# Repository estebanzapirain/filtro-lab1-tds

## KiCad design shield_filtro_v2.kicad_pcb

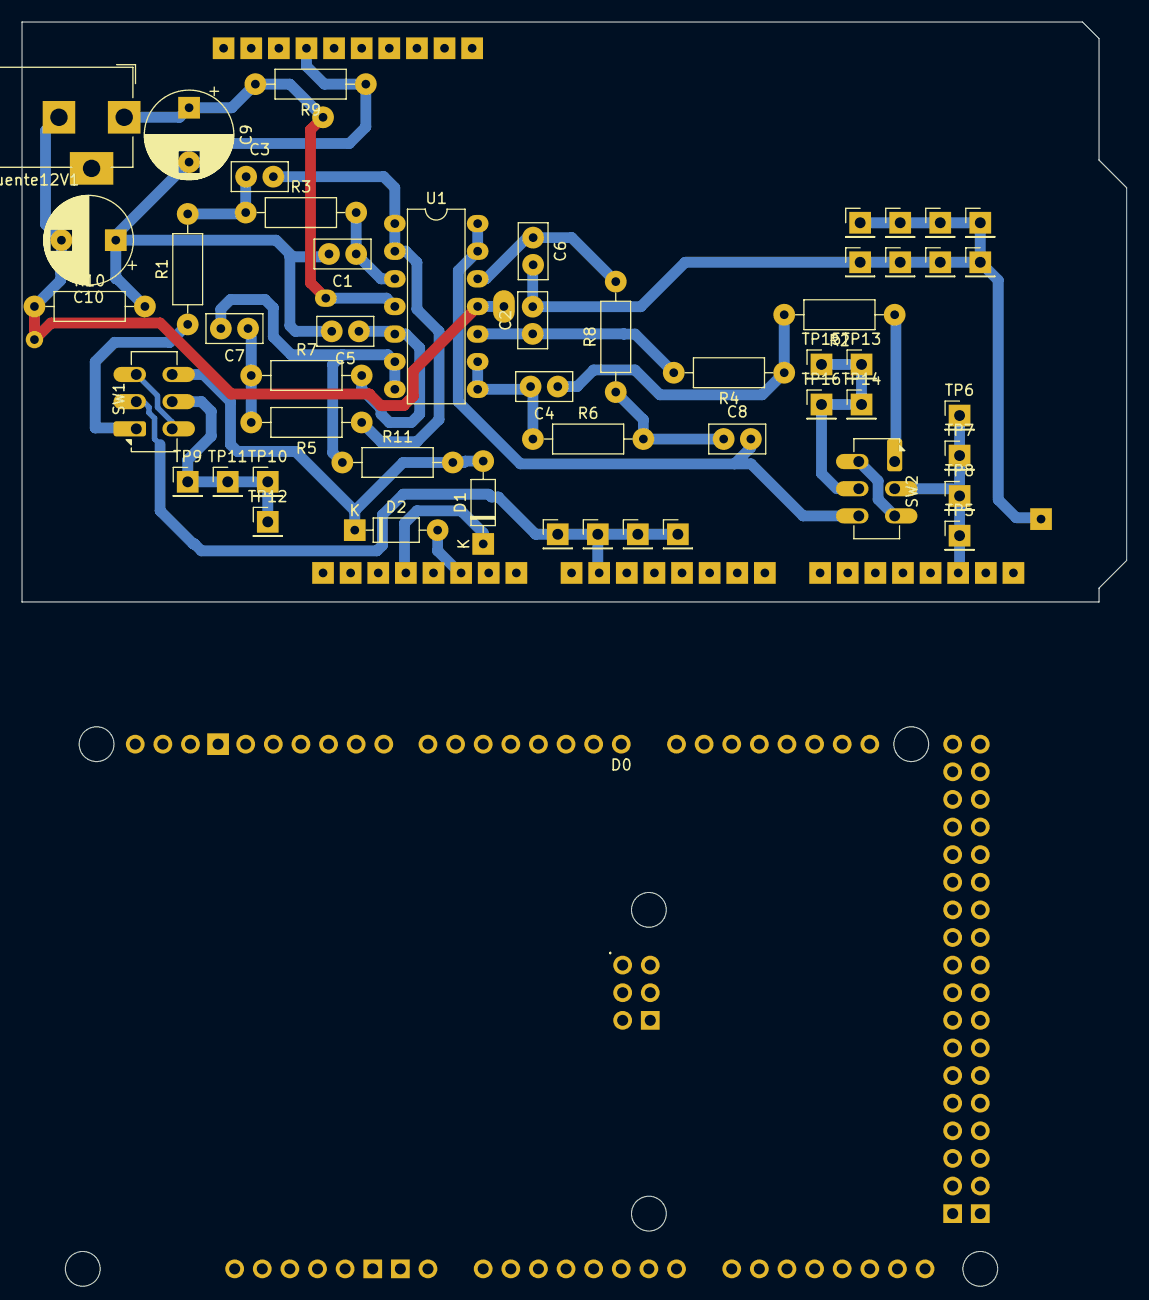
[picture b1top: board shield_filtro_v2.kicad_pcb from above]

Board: 2 copper layers, 101.6 x 53.3 mm, 52 parts (0 on the bottom side), 25 nets.

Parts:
A2: Arduino_Due_Shield
C1, C2: 100p; C_Disc_D5.0mm_W2.5mm_P2.50mm
C3, C4, C7, C8: 1n; C_Disc_D5.0mm_W2.5mm_P2.50mm
C5, C6: 680p; C_Disc_D5.0mm_W2.5mm_P2.50mm
C9, C10: C_Polarized; CP_Radial_D8.0mm_P5.00mm
D1, D2: BAT85; D_DO-35_SOD27_P7.62mm_Horizontal
Fuente12V1: Barrel_Jack_MountingPin; BarrelJack_CUI_PJ-102AH_Horizontal
R1, R2: 47k; R_Axial_DIN0207_L6.3mm_D2.5mm_P10.16mm_Horizontal
R3, R4: 13k; R_Axial_DIN0207_L6.3mm_D2.5mm_P10.16mm_Horizontal
R5, R6: 16k; R_Axial_DIN0207_L6.3mm_D2.5mm_P10.16mm_Horizontal
R7, R8: 6.2k; R_Axial_DIN0207_L6.3mm_D2.5mm_P10.16mm_Horizontal
R9: 10k; R_Axial_DIN0207_L6.3mm_D2.5mm_P10.16mm_Horizontal
R10: 10K; R_Axial_DIN0207_L6.3mm_D2.5mm_P10.16mm_Horizontal
R11: 470; R_Axial_DIN0207_L6.3mm_D2.5mm_P10.16mm_Horizontal
SW1, SW2: SW_DPDT_x2; SW_CK_JS202011CQN_DPDT_Straight
TP1, TP2, TP3, TP4, TP5, TP6, TP7, TP8, TP9, TP10, TP11, TP12, TP13, TP14, TP15, TP16, TP17, TP18, TP19, TP20, TP21, TP22, TP23, TP24: TestPoint; PinHeader_1x01_P2.54mm_Vertical
U1: Opamp_Quad; DIP-14_W7.62mm

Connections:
3V3: A2.3V3 (3.3V), D1.1 (K)
/A1: A2.A1, SW1.2 (B), TP1.1, TP2.1, TP3.1, TP4.1
/A1Filt: SW1.5 (B), TP9.1, TP10.1, TP11.1, TP12.1
/DAC1: A2.DAC1, SW2.2 (B), TP5.1, TP6.1, TP7.1, TP8.1
/DAC1Filt: SW2.5 (B), TP13.1, TP14.1, TP15.1, TP16.1
GND: A2.GND1 (GND), A2.GND2 (GND), A2.GND3 (GND), A2.GND4 (SPI_GND), A2.GND5 (GND), A2.GND6 (GND), C1.2, C2.2, C5.2, C6.2, C9.2, C10.1, D2.2 (A), R9.1, R10.2, TP17.1, TP18.1, TP19.1, TP20.1, TP21.1, TP22.1, TP23.1, TP24.1
unnamed: C3.1, R1.2, R3.1
unnamed: C4.1, R2.2, R4.1
unnamed: C7.1, R5.2, R7.1
unnamed: C8.1, R6.2, R8.1
unnamed: D1.2 (A), D2.1 (K), R11.2, SW1.4 (A)
unnamed: R1.1, SW1.1 (A)
unnamed: SW1.3 (C), SW1.6 (C)
unnamed: R2.1, SW2.1 (A)
unnamed: SW2.3 (C), SW2.6 (C)
unnamed: C8.2, SW2.4 (A), U1.13 (-), U1.14
unnamed: C1.1, R3.2, U1.3 (+)
unnamed: C3.2, R5.1, U1.1, U1.2 (-)
unnamed: C5.1, R7.2, U1.5 (+)
unnamed: C7.2, R11.1, U1.6 (-), U1.7
unnamed: C2.1, R4.2, U1.10 (+)
unnamed: C4.2, R6.1, U1.8, U1.9 (-)
unnamed: C6.1, R8.2, U1.12 (+)
unnamed: C9.1, Fuente12V1.1, R9.2, U1.4 (V+)
unnamed: C10.2, Fuente12V1.2, R10.1, U1.11 (V-)

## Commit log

2024-08-01 Commit de arranque
